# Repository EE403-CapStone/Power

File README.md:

# Power Design Documents
[toc]

----
## General
This part illustrates the design of the power associated with the project. There are two KiCAD project folders. One of them is "403_charger_v1," and another one is "403_charger_v2". "403_charger_v1" is the initial design of the power, but it has some problems with the design. "403_charger_v2" is the design that problems got corrected. In the description of the documents, "403_charger_v2" will be described.

----
## Description
In the KiCAD project folder, there are three main files, which are "403_charger_v2.kicad_pcb", "403_charger_v2.kicad_pro", "403_charger_v2.kicad_sch". "403_charger_v2.kicad_pcb" is the PCB file of the power. "403_charger_v2.kicad_pro" is the project file of the power. "403_charger_v2.kicad_sch" is the schematic file of the power. These three files can only be opened by the KiCAD.    

----
## Schematic
||
|:--:|
|Schematic Preview of the Power|
  
The circuit consists of 3 main circuits: the charging circuit, the protection circuit, and the boost circuit. Details of all components in the schematic will be shown below.    

-----
## PCB
|||
|:--:|:--:|
|PCB Preview of the Power|3D Preview of the PCB|

Three different track widths are used in the PCB design. They are 0.250mm, 0.500mm, and 0.750mm. The track of 0.250mm is used to transfer the signals around the chips. The track of 0.500 mm is used to connect pins involved with the output of the battery. The track of 0.750mm is used to be paths involved with boosted output. Additionally, two copper pour planes of GND are on the front and the back.

----
## Bill of Material
|Number|References|Value|Footprint|Quantity|Price|
|:--:|:--:|:--:|:--:|:--:|:--:|
|1	    	|C3, C4	    |22uF	    |C_1206_3216Metric  |2|US$1.06|
|2			|C1	        |0.1u	    |0603_R	            |1|US$ 0.0026|
|3			|C2	        |10u	    |0603_R	            |1|US$ 0.0063|
|4			|R5, R6, R7	|1k	        |0603_R	            |3|US$ 0.0033|
|5			|R1, R3	    |2k	        |0603_R             |2|US$ 0.0018|
|6			|R2	        |100	    |0603_R	            |1|US$ 0.0012|
|7			|R4	        |7.5k	    |0603_R	            |1|US$ 0.0013|
|8			|L1	        |22uH	    |75_75_4            |1|US$ 0.1676|
|9			|D1	        |SS34_mdd	|SS34	            |1|US$ 0.0342|
|10			|D2	        |LED_R	    |0603_LED_S1        |1|US$ 0.0381|
|11			|D3	        |LED_G	    |0603_LED_S1        |1|US$ 0.0381|
|12			|U1	        |TP4056_[C16581]	|SOP-8_EP_150MIL    |1|US$ 0.2303|
|13			|U2	        |MT3608	    |SOT-23-6	                |1|US$ 0.1627|
|14			|SW1	    |SW_DIP_x01	        |SW_500SSP3S1M6QEA  |1|US$3.89|
|15			|IC1	    |FS312F-G	        |SOT-23-6   |1|US$ 0.16|
|16			|Q1	        |FS8205             |SOT-23-6   |1|US$ 0.1763|
|17			|J2, J3	    |Conn_01x02_Female	|SolderWire-1sqmm_1x02_P5.4mm_D1.4mm_OD2.7mm    |2|free|
|18	        |J1	        |USB_B_Micro	    |USB_Micro-B_Amphenol_10103594-0001LF_Horizontal|1|free|
  
There is also another interactive BOM in the files. The path is "403_charger_v2\bom\ibom.html". In the "ibom.html," you can click the component on the PCB then the corresponding information of the component will be highlighted at the side. The following figure is the preview of the interactive BOM.
  
||
|:--:|
|Preview of the Interactive BOM|

<!-- ## Update History
### 09.13.22 Update
1. The folder, "403_charger_v1", has been uploaded.
2. The 1st version of design has been finished and its draft schematic has been uploaded.  
3. All chips were purchased on 09.05.22. Approximately they will arrive here on 09.19.22.  
4. Next step is going to test these chips and check if the schematic is approachable. If the schematic can work very well, the PCB board will be planned to finish.   
5. The better design is looked for as the alternative case during the waiting time for chips.   

### 09.30.22 Update
1. The footprints of all components have been verified.
2. The routing of the PCB has been finished.
3. BOM file is in the following path: 403_charger_v1/bom/ibom.html.

### 10.03.22 Update
1. Gerber files of the PCB have been ouputed and uploaded.
2. The PCB board has been in the production.

### 10.24.22 Update
1. The folder, "403_charger_v2", has been uploaded.
1. Errors on footprints have been corrected.
2. The spacing and track width have been increased.
3. Four mounting holes have been added into the PCB. -->

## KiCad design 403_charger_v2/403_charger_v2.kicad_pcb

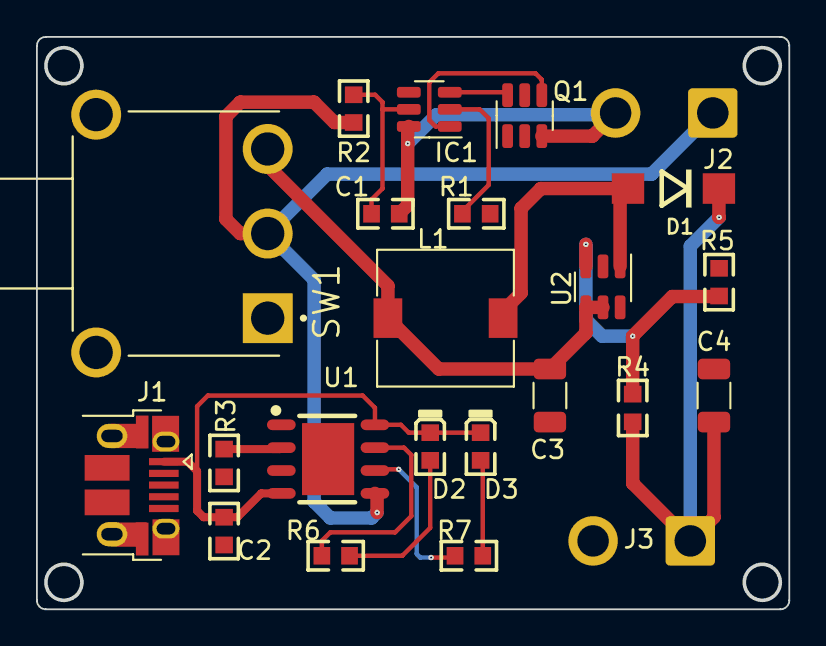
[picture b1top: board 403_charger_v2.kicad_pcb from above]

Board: 2 copper layers, 41.7 x 31.7 mm, 23 parts (0 on the bottom side), 17 nets.

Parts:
C1: 0.1u; 0603_R
C2: 10u; 0603_R
C3, C4: 22uF; C_1206_3216Metric
D1: SS34_mdd; SS34
D2: LED_R; 0603_LED_S1
D3: LED_G; 0603_LED_S1
IC1: FS312F-G; SOT-23-6
J1: USB_B_Micro; USB_Micro-B_Amphenol_10103594-0001LF_Horizontal
J2, J3: Conn_01x02_Female; SolderWire-1sqmm_1x02_P5.4mm_D1.4mm_OD2.7mm
L1: 22uH; 75_75_4
Q1: FS8205; SOT-23-6
R1, R3: 2k; 0603_R
R2: 100; 0603_R
R4: 7.5k; 0603_R
R5, R6, R7: 1k; 0603_R
SW1: SW_DIP_x01; SW_500SSP3S1M6QEA
U1: TP4056_[C16581]; SOP-8_EP_150MIL
U2: MT3608; SOT-23-6

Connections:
/5V: C4.1, D1.C, J3.1, R4.1
/BAT+: J2.1, R2.2, SW1.2, U1.5 (BAT)
/BAT-: C1.2, IC1.6 (GND), J2.2, Q1.3 (S)
/OD: IC1.1 (OD), Q1.4 (G)
/VBUS: C2.1, D2.2 (A), D3.2 (A), J1.1 (VBUS), U1.4 (VCC), U1.8 (CE)
GND: C2.2, C3.2, C4.2, J1.5 (GND), J1.6 (Shield), J3.2, Q1.1 (S), R1.1, R3.1, R5.2, U1.1 (TEMP), U1.3 (GND), U2.2 (GND)
unnamed: C1.1, IC1.5 (VCC), R2.1
unnamed: C3.1, L1.2, SW1.3, U2.4 (EN), U2.5 (IN)
unnamed: D1.A, L1.1, U2.1 (SW)
unnamed: D2.1 (K), R6.2
unnamed: D3.1 (K), R7.2
unnamed: IC1.2 (CS), R1.2
unnamed: IC1.3 (OC), Q1.6 (G)
unnamed: R3.2, U1.2 (PROG)
unnamed: R4.2, R5.1, U2.3 (FB)
unnamed: R6.1, U1.7 (~CHRG)
unnamed: R7.1, U1.6 (~STDBY)

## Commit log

2022-09-13 second commit
2022-09-16 09.15 Update
2022-10-01 09/30/22
2022-10-03 Gerber Files Updated
2022-10-03 Gerber Files Update
2022-10-24 10.24 Update
2022-10-27 10/27 update
